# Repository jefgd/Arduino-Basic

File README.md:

# Arduino-Basic
This is a very basic Arduino circuit that includes analog a digital pins for using on a project that may require a microcontroller permanently, and it was created using through hole components.
The KiCad files will be added (schematic, .lib, .net, etc) and on a different folder the GERBER and drill files.
The Gcode was done with FlatCam and those files will be added also.

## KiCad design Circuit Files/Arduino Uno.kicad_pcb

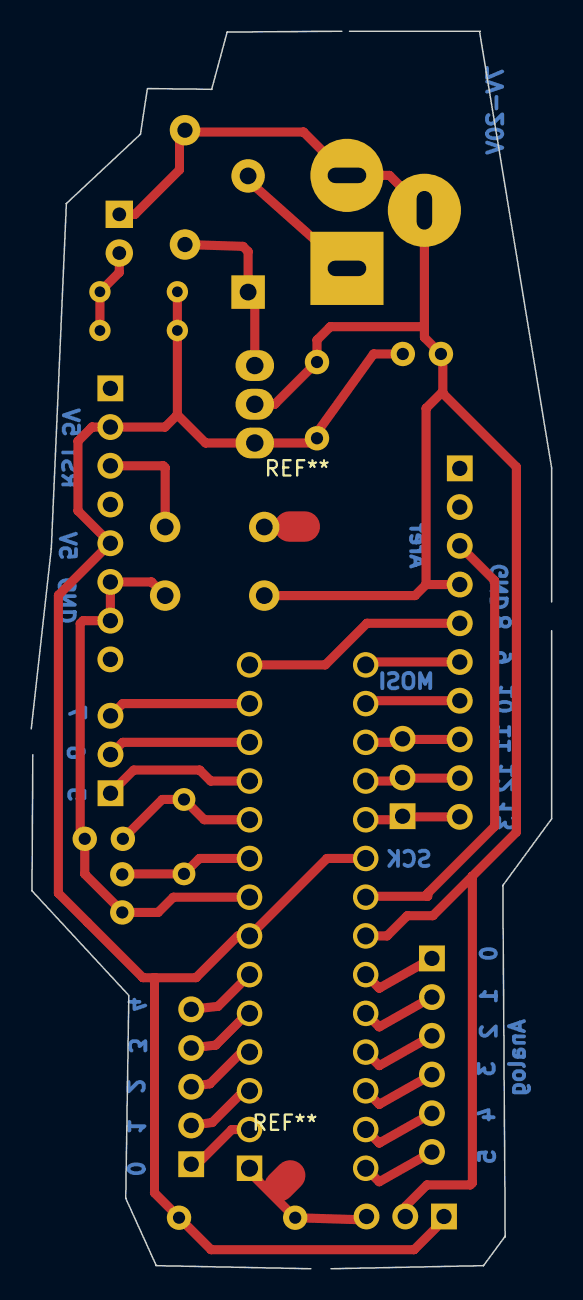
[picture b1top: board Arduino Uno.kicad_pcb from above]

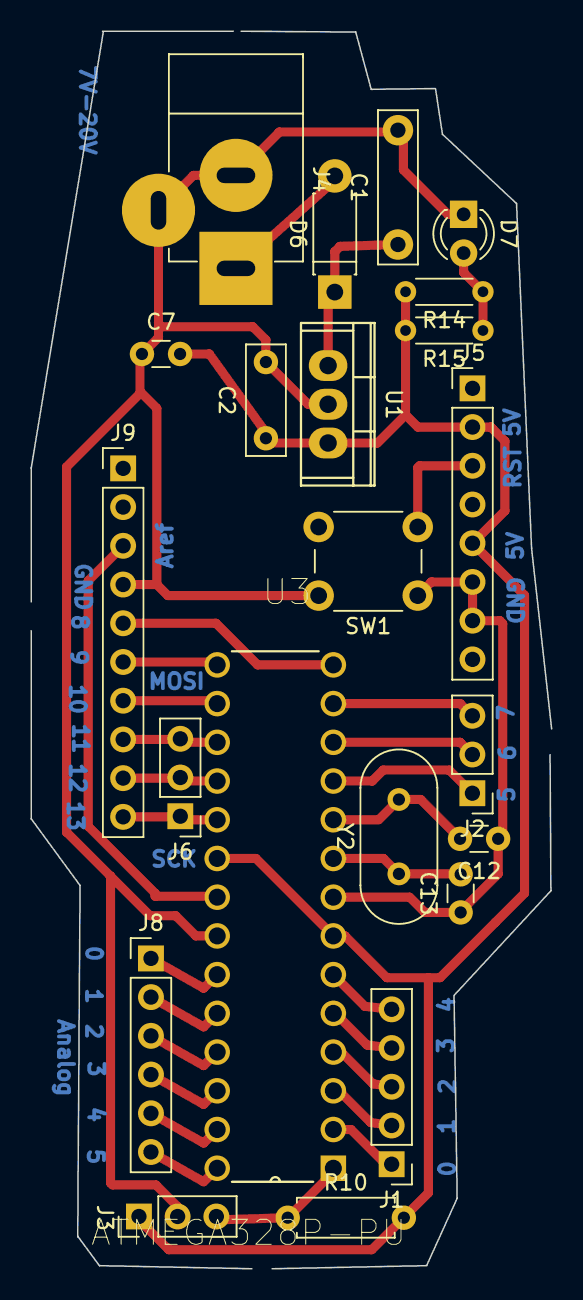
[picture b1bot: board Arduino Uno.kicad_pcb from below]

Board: 2 copper layers, 34.1 x 81.2 mm, 22 parts (22 on the bottom side), 28 nets.

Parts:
C1: C; C_Rect_L10.0mm_W2.5mm_P7.50mm_MKS4
C2: C; C_Rect_L7.2mm_W2.5mm_P5.00mm_FKS2_FKP2_MKS2_MKP2
C7, C12, C13: C_Small; C_Disc_D3.0mm_W1.6mm_P2.50mm
D6: D; D_DO-41_SOD81_P7.62mm_Horizontal
D7: LED; LED_D3.0mm
J1: Conn_01x05_Female; Socket_Strip_Straight_1x05_Pitch2.54mm
J2: Conn_01x03_Female; Socket_Strip_Straight_1x03_Pitch2.54mm
J3, J6: Conn_01x03_Male; Pin_Header_Straight_1x03_Pitch2.54mm
J4: Barrel_Jack; JACK_ALIM
J5: Conn_01x08_Female; Socket_Strip_Straight_1x08_Pitch2.54mm
J8: Conn_01x06_Female; Socket_Strip_Straight_1x06_Pitch2.54mm
J9: Conn_01x10_Female; Socket_Strip_Straight_1x10_Pitch2.54mm
R10: R; R_Axial_DIN0207_L6.3mm_D2.5mm_P7.62mm_Horizontal
R14, R15: R; R_Axial_DIN0204_L3.6mm_D1.6mm_P5.08mm_Horizontal
SW1: SW_Push; SW_PUSH_6mm_h5mm
U1: LM7805_TO220; TO-220
U3: ATMEGA328P-PU; DIP254P762X457-28
Y2: Crystal; Crystal_HC49-4H_Vertical

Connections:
+5V: D6.2, J4.1
AREF: J9.3, U3.21
GND: C1.2, C2.2, C7.1, C12.1, C13.1, D7.1, J3.2, J4.2, J4.3, J5.6, J5.7, J9.4, SW1.1, U1.2, U3.8, U3.22
unnamed: C1.1, D6.1, U1.1
unnamed: C12.2, U3.10, Y2.2
unnamed: C13.2, U3.9, Y2.1
unnamed: D7.2, R14.1, R15.1
unnamed: J1.1, U3.2
unnamed: J1.2, U3.3
unnamed: J1.3, U3.4
unnamed: J1.4, U3.5
unnamed: J1.5, U3.6
unnamed: J2.1, U3.11
unnamed: J2.2, U3.12
unnamed: J2.3, U3.13
unnamed: J6.1, J9.10, U3.19
unnamed: J6.2, J9.9, U3.18
unnamed: J6.3, J9.8, U3.17
unnamed: J8.1, U3.23
unnamed: J8.2, U3.24
unnamed: J8.3, U3.25
unnamed: J8.4, U3.26
unnamed: J8.5, U3.27
unnamed: J8.6, U3.28
unnamed: J9.5, U3.14
unnamed: J9.6, U3.15
unnamed: J9.7, U3.16
RESET: C2.1, C7.2, J3.1, J3.3, J5.2, J5.3, J5.5, R10.1, R10.2, R14.2, R15.2, SW1.2, U1.3, U3.1, U3.7, U3.20

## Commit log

2019-11-13 repo reupload
    Repo reupload
    C:/Users/ciscotec/Desktop/git/Arduino-Basic/.git/COMMIT_EDITMSG[+] [unix] (20:13 12/11/2019) 11,0-1 Todowq
2019-11-13 Revision 0.1
